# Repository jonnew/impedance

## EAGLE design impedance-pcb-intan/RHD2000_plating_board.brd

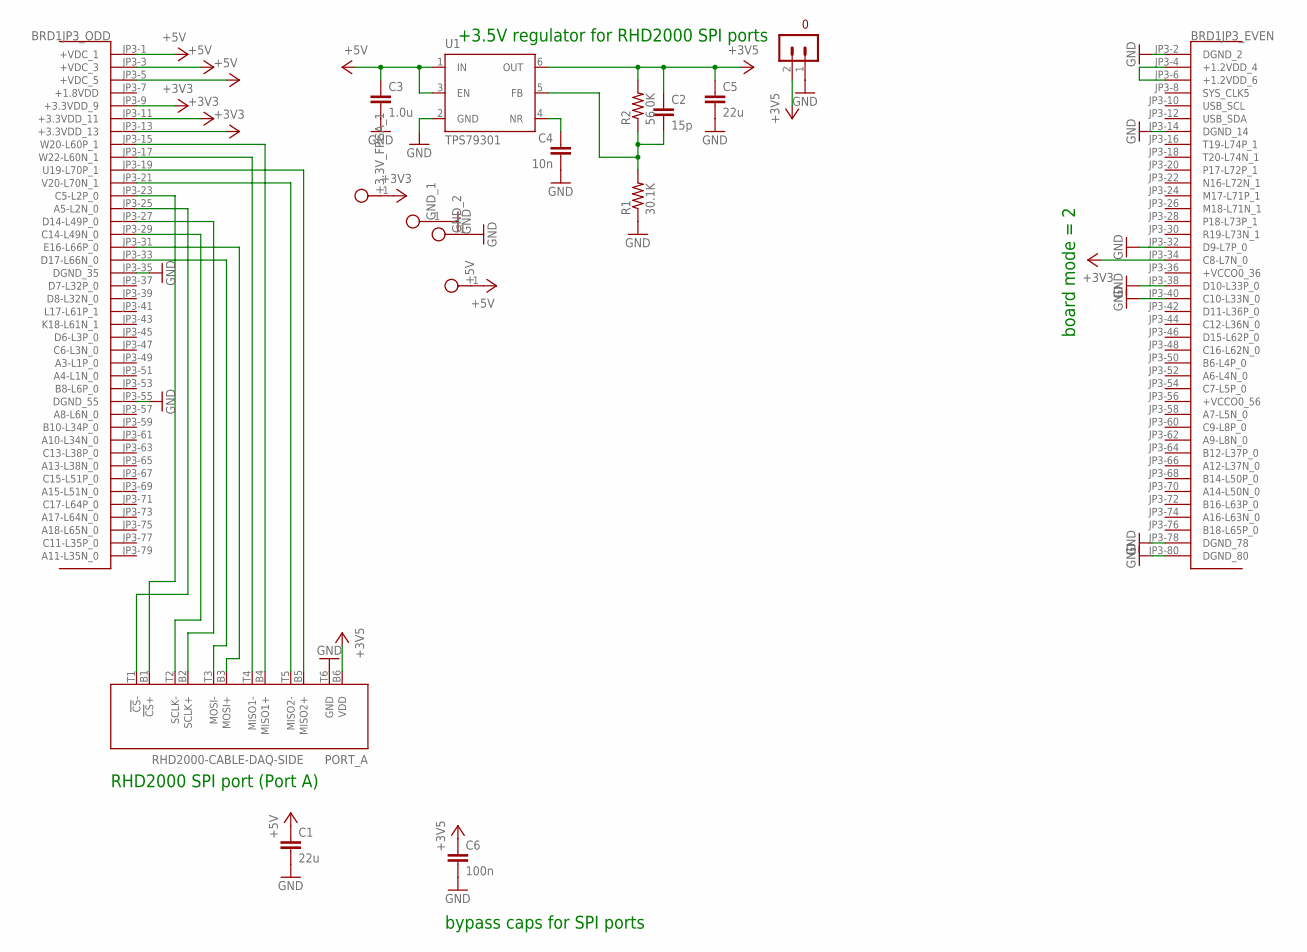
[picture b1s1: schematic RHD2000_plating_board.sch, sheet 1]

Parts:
+3.3V_FPGA_1, +5V: TESTPOINT
BRD1: OPALKELLY_XEM6010
C1, C5: 22u; 1206
C2: 15p; 0603
C3: 1.0u; 0805
C4: 10n; 0603
C6: 100n; 0603
GND_1, GND_2: TESTPOINT
PORT_A: RHD2000-CABLE-DAQ-SIDE; OMNETICS_PZN-12-AA
R1: 30.1K; 0603
R2: 56.0K; 0603
S2: TERMINAL_BLOCK_2-3.5MM-3.5V; TERMINAL_BLOCK_3.5MM_2_3.5V
U1: TPS79301; SOT-23-6

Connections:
+1.8VDD: BRD1.JP3-7 (+1.8VDD)
+3V3: +3.3V_FPGA_1.1, BRD1.JP3-9 (+3.3VDD_9), BRD1.JP3-11 (+3.3VDD_11), BRD1.JP3-13 (+3.3VDD_13), BRD1.JP3-34 (C8-L7N_0); also elsewhere on the board
+3V5: C2.1, C5.1, C6.1, PORT_A.B6 (VDD), R2.2, S2.2 (1), U1.6 (OUT)
+5V: +5V.1, BRD1.JP3-1 (+VDC_1), BRD1.JP3-3 (+VDC_3), BRD1.JP3-5 (+VDC_5), C1.1, C3.1, U1.1 (IN), U1.3 (EN); also elsewhere on the board
+VCCO0_36: BRD1.JP3-36 (+VCCO0_36)
+VCCO0_56: BRD1.JP3-56 (+VCCO0_56)
+VCCO1_35: BRD1.JP2-35 (+VCCO1_35)
+VCCO1_55: BRD1.JP2-55 (+VCCO1_55)
GND: BRD1.JP3-2 (DGND_2), BRD1.JP3-14 (DGND_14), BRD1.JP3-32 (D9-L7P_0), BRD1.JP3-35 (DGND_35), BRD1.JP3-38 (D10-L33P_0), BRD1.JP3-40 (C10-L33N_0), BRD1.JP3-55 (DGND_55), BRD1.JP3-78 (DGND_78), BRD1.JP3-80 (DGND_80), C1.2, C3.2, C4.2, C5.2, C6.2, GND_1.1, GND_2.1, PORT_A.T6 (GND), R1.1, S2.1 (0), U1.2 (GND); also elsewhere on the board
unnamed: BRD1.JP3-15 (W20-L60P_1), PORT_A.B4 (MISO1+)
unnamed: BRD1.JP3-17 (W22-L60N_1), PORT_A.T4 (MISO1-)
unnamed: BRD1.JP3-19 (U19-L70P_1), PORT_A.B5 (MISO2+)
unnamed: BRD1.JP3-21 (V20-L70N_1), PORT_A.T5 (MISO2-)
unnamed: BRD1.JP3-23 (C5-L2P_0), PORT_A.B1 (!CS!+)
unnamed: BRD1.JP3-25 (A5-L2N_0), PORT_A.T1 (!CS!-)
unnamed: BRD1.JP3-27 (D14-L49P_0), PORT_A.B2 (SCLK+)
unnamed: BRD1.JP3-29 (C14-L49N_0), PORT_A.T2 (SCLK-)
unnamed: BRD1.JP3-31 (E16-L66P_0), PORT_A.B3 (MOSI+)
unnamed: BRD1.JP3-33 (D17-L66N_0), PORT_A.T3 (MOSI-)
unnamed: C4.1, U1.4 (NR)
unnamed: C2.2, R1.2, R2.1, U1.5 (FB)
unnamed: BRD1.JP3-4 (+1.2VDD_4), BRD1.JP3-6 (+1.2VDD_6)

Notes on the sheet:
+3.5V regulator for RHD2000 SPI ports
RHD2000 SPI port (Port A)
board mode = 2
bypass caps for SPI ports

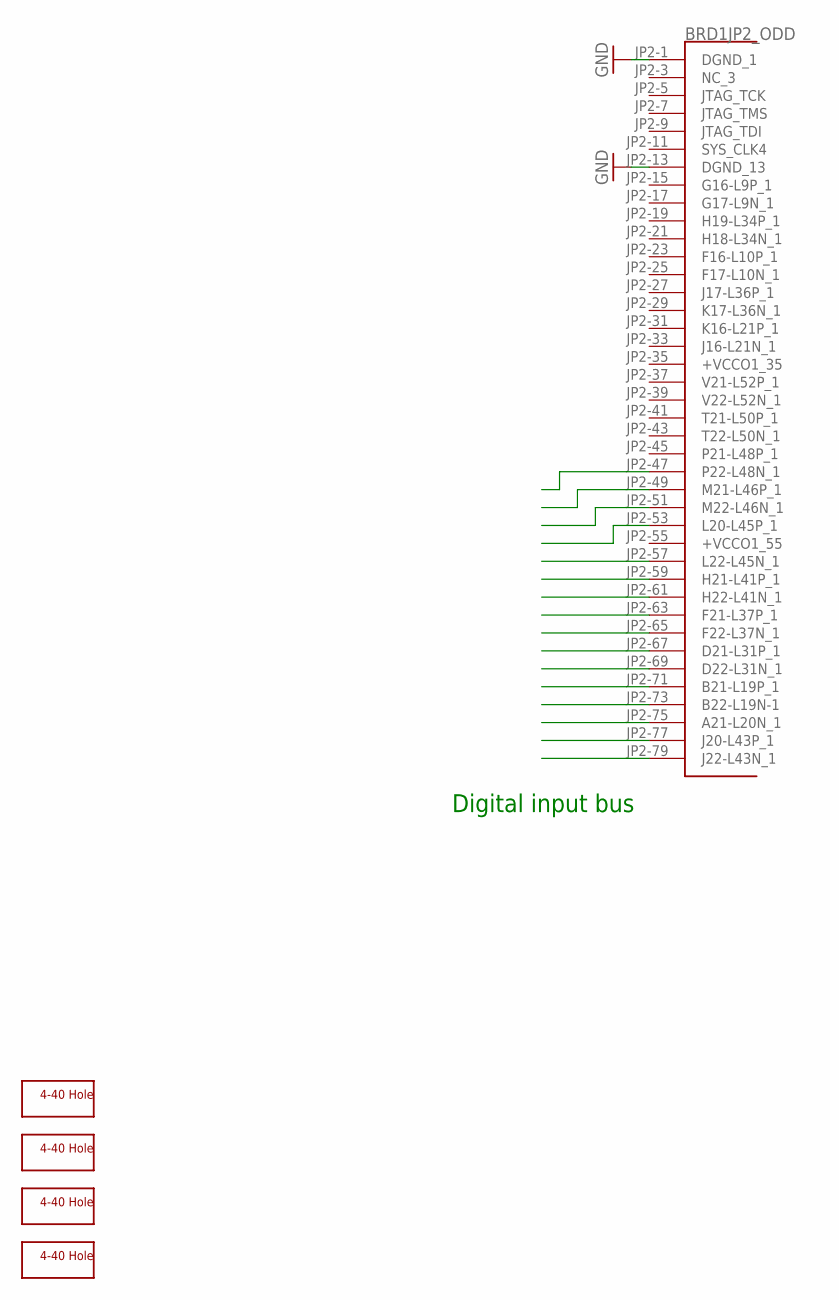
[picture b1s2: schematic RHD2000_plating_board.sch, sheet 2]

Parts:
BRD1: OPALKELLY_XEM6010
H1, H2, H3, H4: SCREW_HOLE_4-40

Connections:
+1.8VDD: BRD1.JP3-7 (+1.8VDD)
+VCCO0_36: BRD1.JP3-36 (+VCCO0_36)
+VCCO0_56: BRD1.JP3-56 (+VCCO0_56)
+VCCO1_35: BRD1.JP2-35 (+VCCO1_35)
+VCCO1_55: BRD1.JP2-55 (+VCCO1_55)
GND: BRD1.JP2-1 (DGND_1), BRD1.JP2-13 (DGND_13); also elsewhere on the board

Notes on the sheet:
Digital input bus

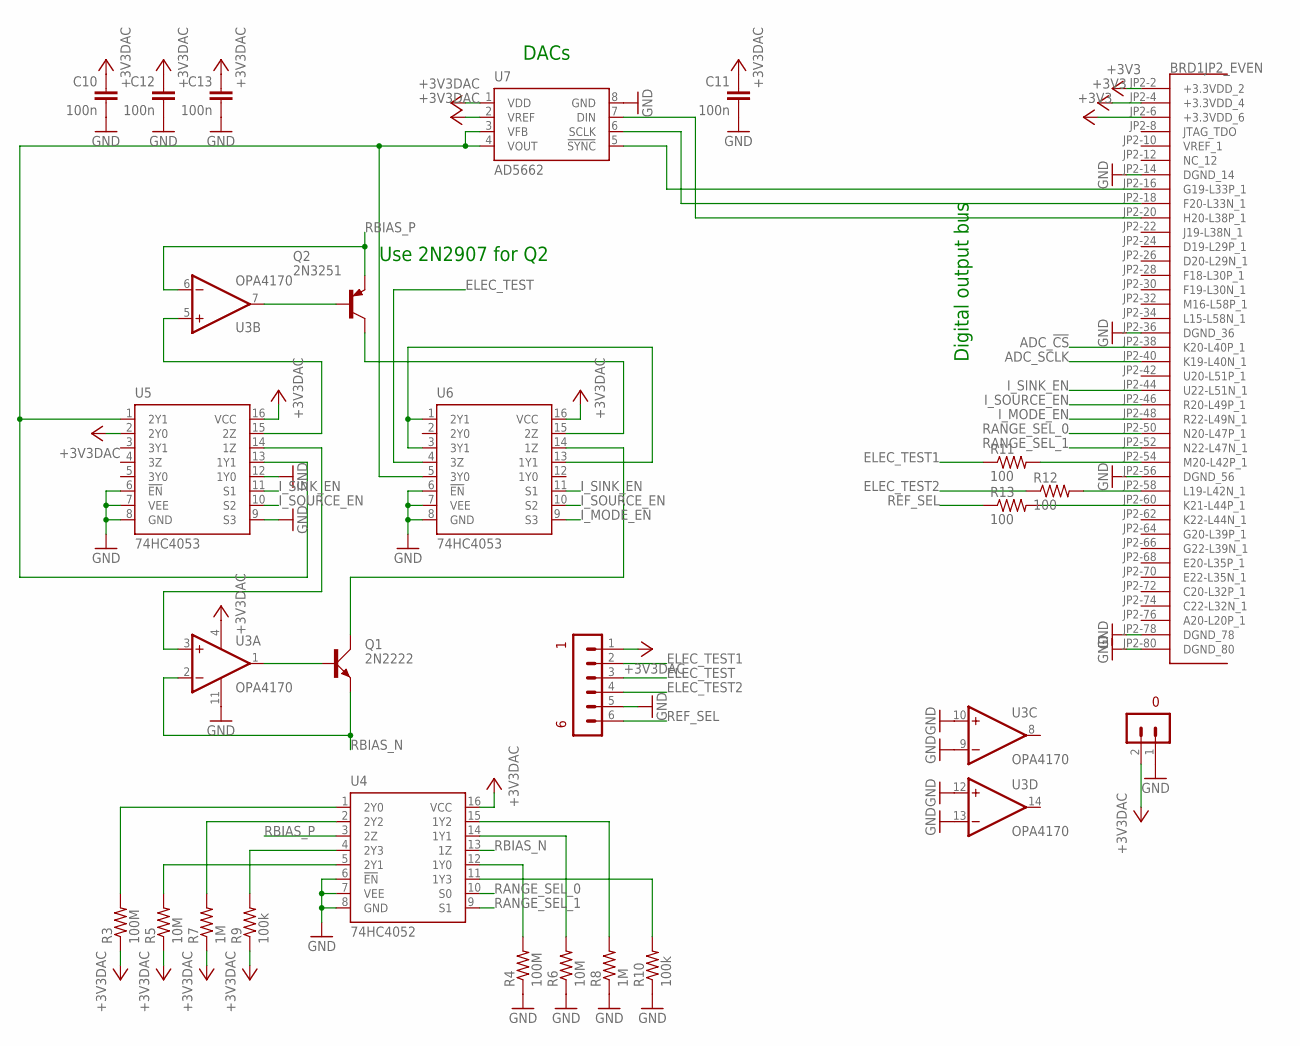
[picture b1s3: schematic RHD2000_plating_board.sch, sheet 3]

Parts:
BRD1: OPALKELLY_XEM6010
C10, C11, C12, C13: 100n; 0603
Q1: 2N2222; TO18A
Q2: 2N3251; TO18
R3, R4: 100M; 1206
R5, R6: 10M; 0603
R7, R8: 1M; 0603
R9, R10: 100k; 0603
R11, R12, R13: 100; 0603
S1: TERMINAL_BLOCK_2-3.5MM-3.3V; TERMINAL_BLOCK_3.5MM_2_3.3V
S3: WIRES-6
U3: OPA4170; SOIC-14
U4: 74HC4052; TSSOP-16
U5, U6: 74HC4053; TSSOP-16
U7: AD5662; SOT-23-RJ-8

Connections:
+1.8VDD: BRD1.JP3-7 (+1.8VDD)
+3V3: BRD1.JP2-2 (+3.3VDD_2), BRD1.JP2-4 (+3.3VDD_4), BRD1.JP2-6 (+3.3VDD_6); also elsewhere on the board
+3V3DAC: C10.1, C11.1, C12.1, C13.1, R3.1, R5.1, R7.1, R9.1, S1.2 (1), S3.1, U3.4 (V+), U4.16 (VCC), U5.2 (2Y0), U5.16 (VCC), U6.16 (VCC), U7.1 (VDD), U7.2 (VREF); also elsewhere on the board
+VCCO0_36: BRD1.JP3-36 (+VCCO0_36)
+VCCO0_56: BRD1.JP3-56 (+VCCO0_56)
+VCCO1_35: BRD1.JP2-35 (+VCCO1_35)
+VCCO1_55: BRD1.JP2-55 (+VCCO1_55)
ADC_!CS!: BRD1.JP2-38 (K20-L40P_1)
ADC_SCLK: BRD1.JP2-40 (K19-L40N_1)
ELEC_TEST: S3.3, U6.4 (3Z)
ELEC_TEST1: R11.1, S3.2
ELEC_TEST2: R12.1, S3.4
GND: BRD1.JP2-14 (DGND_14), BRD1.JP2-36 (DGND_36), BRD1.JP2-56 (DGND_56), BRD1.JP2-78 (DGND_78), BRD1.JP2-80 (DGND_80), C10.2, C11.2, C12.2, C13.2, R4.1, R6.1, R8.1, R10.1, S1.1 (0), S3.5, U3.9 (-IN), U3.10 (+IN), U3.11 (V-), U3.12 (+IN), U3.13 (-IN), U4.6 (!EN!), U4.7 (VEE), U4.8 (GND), U5.6 (!EN!), U5.7 (VEE), U5.8 (GND), U5.9 (S3), U5.12 (1Y0), U6.6 (!EN!), U6.7 (VEE), U6.8 (GND), U7.8 (GND); also elsewhere on the board
I_MODE_EN: BRD1.JP2-48 (R22-L49N_1), U6.9 (S3)
I_SINK_EN: BRD1.JP2-44 (U22-L51N_1), U5.11 (S1), U6.11 (S1)
I_SOURCE_EN: BRD1.JP2-46 (R20-L49P_1), U5.10 (S2), U6.10 (S2)
unnamed: Q1.B, U3.1 (OUT)
unnamed: U5.1 (2Y1), U5.13 (1Y1), U6.5 (3Y0), U7.3 (VFB), U7.4 (VOUT)
unnamed: U3.3 (+IN), U5.14 (1Z)
unnamed: Q1.C, U6.14 (1Z)
unnamed: U3.5 (+IN), U5.15 (2Z)
unnamed: Q2.2 (B), U3.7 (OUT)
unnamed: Q2.3 (C), U6.15 (2Z)
unnamed: BRD1.JP2-54 (M20-L42P_1), R11.2
unnamed: BRD1.JP2-58 (L19-L42N_1), R12.2
unnamed: R9.2, U4.4 (2Y3)
unnamed: R7.2, U4.2 (2Y2)
unnamed: R5.2, U4.5 (2Y1)
unnamed: R3.2, U4.1 (2Y0)
unnamed: R4.2, U4.12 (1Y0)
unnamed: R6.2, U4.14 (1Y1)
unnamed: R8.2, U4.15 (1Y2)
unnamed: R10.2, U4.11 (1Y3)
unnamed: U6.1 (2Y1), U6.3 (3Y1), U6.13 (1Y1)
unnamed: BRD1.JP2-60 (K21-L44P_1), R13.2
unnamed: BRD1.JP2-16 (G19-L33P_1), U7.5 (!SYNC!)
unnamed: BRD1.JP2-18 (F20-L33N_1), U7.6 (SCLK)
unnamed: BRD1.JP2-20 (H20-L38P_1), U7.7 (DIN)
RANGE_SEL_0: BRD1.JP2-50 (N20-L47P_1), U4.10 (S0)
RANGE_SEL_1: BRD1.JP2-52 (N22-L47N_1), U4.9 (S1)
RBIAS_N: Q1.E, U3.2 (-IN), U4.13 (1Z)
RBIAS_P: Q2.1 (E), U3.6 (-IN), U4.3 (2Z)
REF_SEL: R13.1, S3.6

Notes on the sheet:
DACs
Digital output bus
Use 2N2907 for Q2

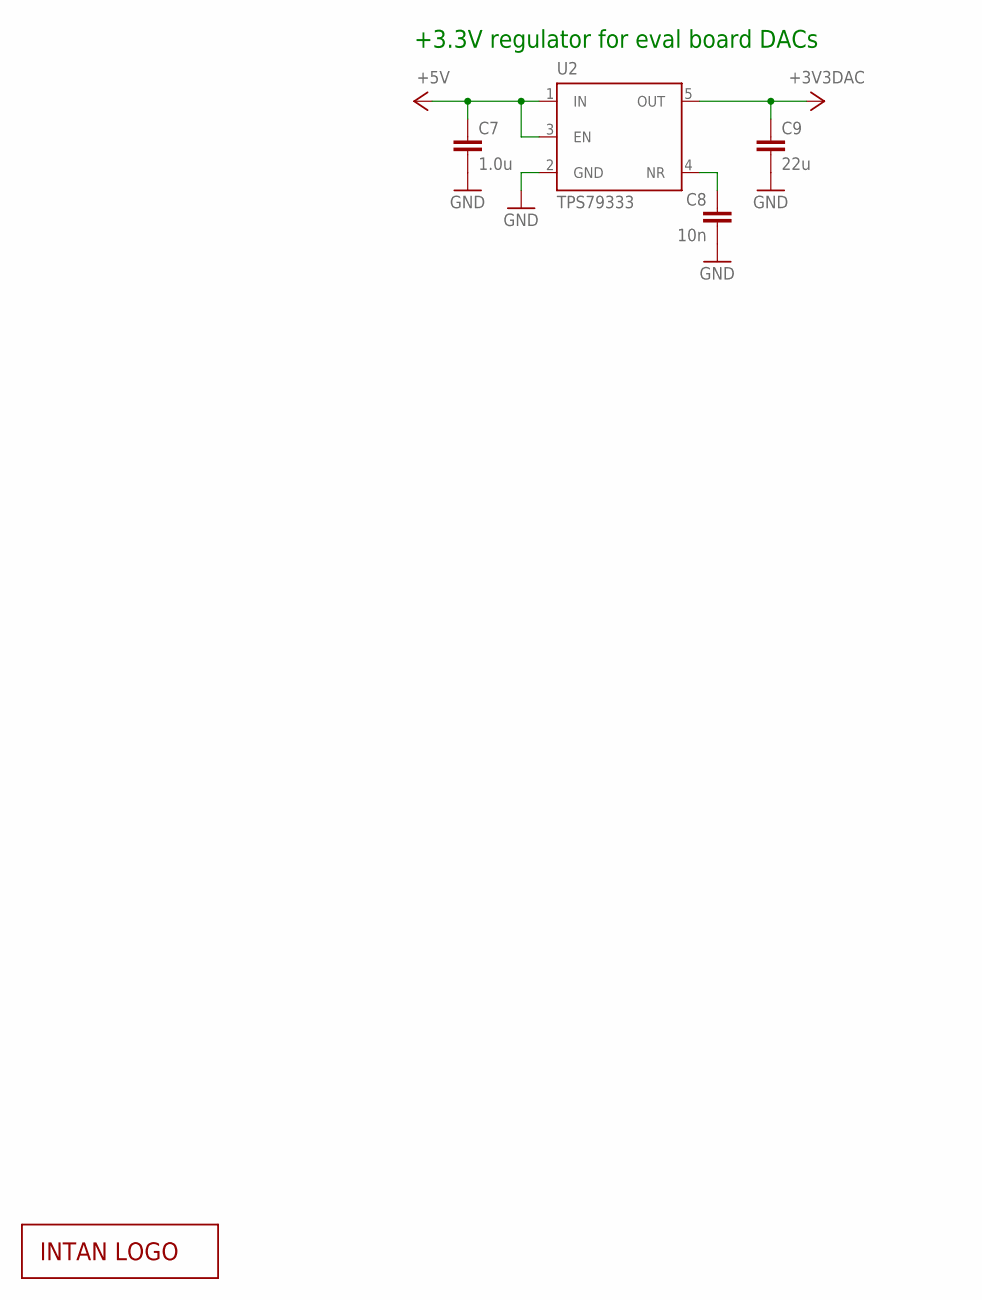
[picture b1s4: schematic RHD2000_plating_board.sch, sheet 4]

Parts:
C7: 1.0u; 0805
C8: 10n; 0603
C9: 22u; 1206
LOGO1: INTAN_LOGO
U2: TPS79333; SOT-23-5

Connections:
+3V3DAC: C9.1, U2.5 (OUT); also elsewhere on the board
+5V: C7.1, U2.1 (IN), U2.3 (EN); also elsewhere on the board
GND: C7.2, C8.2, C9.2, U2.2 (GND); also elsewhere on the board
unnamed: C8.1, U2.4 (NR)

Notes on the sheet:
+3.3V regulator for eval board DACs

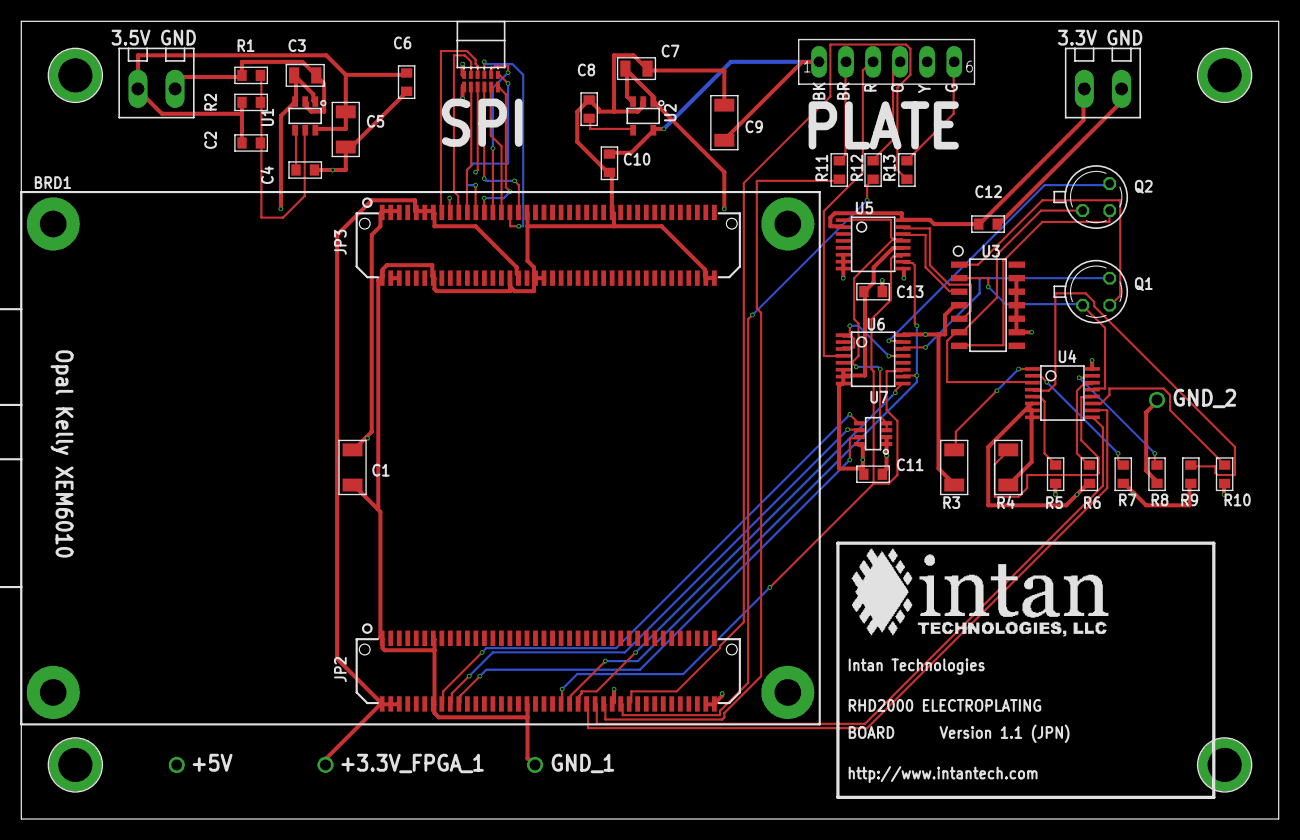
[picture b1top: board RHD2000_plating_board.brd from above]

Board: 4 copper layers, 118.1 x 74.9 mm, 49 parts (0 on the bottom side), 52 nets.

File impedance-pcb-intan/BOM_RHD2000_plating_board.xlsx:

Bill of Materials |  | RHD2000 Plating Board |  | Intan Technologies, LLC
Part | Value | Device | Package | Digi-Key part number | Notes | X (mm) | Y (mm) | Angle | Side | SMD/thru-hole
BRD1 | XEM6010-LX45 | USB/FPGA interface board | module | Opal Kelly XEM6010-LX45 | do not populate
C1 | 22 uF | ceramic capacitor | 1206 | 490-5527-1-ND |  | 31.12 | 33.020000000000003 | 270 | top | SMD
C2 | 15 pF | ceramic capacitor | 0603 | 399-1051-1-ND |  | 21.59 | 63.5 | 0 | top | SMD
C3 | 1.0 uF | ceramic capacitor | 0805 | 587-2910-1-ND |  | 26.67 | 69.849999999999994 | 0 | top | SMD
C4 | 10 nF | ceramic capacitor | 0603 | 478-1227-1-ND |  | 26.67 | 60.96 | 0 | top | SMD
C5 | 22 uF | ceramic capacitor | 1206 | 490-5527-1-ND |  | 30.48 | 64.77 | 270 | top | SMD
C6 | 100 nF | ceramic capacitor | 0603 | 490-1524-1-ND |  | 36.200000000000003 | 69.22 | 270 | top | SMD
C7 | 1.0 uF | ceramic capacitor | 0805 | 587-2910-1-ND |  | 57.79 | 70.48 | 0 | top | SMD
C8 | 10 nF | ceramic capacitor | 0603 | 478-1227-1-ND |  | 53.34 | 66.67 | 90 | top | SMD
C9 | 22 uF | ceramic capacitor | 1206 | 490-5527-1-ND |  | 66.040000000000006 | 65.41 | 90 | top | SMD
C10 | 100 nF | ceramic capacitor | 0603 | 490-1524-1-ND |  | 55.25 | 61.6 | 270 | top | SMD
C11 | 100 nF | ceramic capacitor | 0603 | 490-1524-1-ND |  | 80.010000000000005 | 32.380000000000003 | 180 | top | SMD
C12 | 100 nF | ceramic capacitor | 0603 | 490-1524-1-ND |  | 90.81 | 55.88 | 0 | top | SMD
C13 | 100 nF | ceramic capacitor | 0603 | 490-1524-1-ND |  | 80.010000000000005 | 49.53 | 180 | top | SMD
JP2 | Samtec BTE-040-01-F-D-A | 80-pin connector | SMD 0.8mm pitch | Newark 89M7080 |  | 49.53 | 13.97 | 0 | top | SMD
JP3 | Samtec BTE-040-01-F-D-A | 80-pin connector | SMD 0.8mm pitch | Newark 89M7080 |  | 49.53 | 53.85 | 0 | top | SMD
PORT A | PZN-12-AA | nano connector | polarized 12-pin | Omnetics A79623-001 |  | 43.18 | 69.33 | 0 | top | SMD
Q1 | BC107 | NPN bipolar transistor | TO-18-3 | BC107CS-ND |  | 100.97 | 49.53 | 0 | top | thru-hole | or 2N2222
Q2 | 2N3964 | PNP bipolar transistor | TO-18-3 | 2N3964-ND |  | 100.97 | 58.42 | 0 | top | thru-hole | or 2N2907
R1 | 30.1K (1%) | resistor | 0603 | P30.1KHCT-ND |  | 21.59 | 69.849999999999994 | 0 | top | SMD
R2 | 56.0K (1%) | resistor | 0603 | P56.0KHCT-ND |  | 21.59 | 67.31 | 180 | top | SMD
R3 | 100M (1%) | resistor | 1206 | CRHV100MACT-ND |  | 87.63 | 33.020000000000003 | 90 | top | SMD
R4 | 100M (1%) | resistor | 1206 | CRHV100MACT-ND |  | 92.71 | 33.020000000000003 | 90 | top | SMD
R5 | 10.0M (1%) | resistor | 0603 | 541-10.0MHCT-ND |  | 97.16 | 32.380000000000003 | 90 | top | SMD
R6 | 10.0M (1%) | resistor | 0603 | 541-10.0MHCT-ND |  | 100.33 | 32.380000000000003 | 90 | top | SMD
R7 | 1.00M (1%) | resistor | 0603 | P1.00MHCT-ND |  | 103.51 | 32.380000000000003 | 90 | top | SMD
R8 | 1.00M (1%) | resistor | 0603 | P1.00MHCT-ND |  | 106.68 | 32.380000000000003 | 90 | top | SMD
R9 | 100K (1%) | resistor | 0603 | 541-100KHCT-ND |  | 109.86 | 32.380000000000003 | 90 | top | SMD
R10 | 100K (1%) | resistor | 0603 | 541-100KHCT-ND |  | 113.03 | 32.380000000000003 | 90 | top | SMD
R11 | 100 | resistor | 0603 | P100GCT-ND |  | 76.84 | 60.96 | 270 | top | SMD
R12 | 100 | resistor | 0603 | P100GCT-ND |  | 80.010000000000005 | 60.96 | 270 | top | SMD
R13 | 100 | resistor | 0603 | P100GCT-ND |  | 83.19 | 60.96 | 270 | top | SMD
S1 | 2-pin | terminal block | 3.5mm thru-hole | ED1514-ND |  | 101.6 | 68.58 | 180 | top | thru-hole
S2 | 2-pin | terminal block | 3.5mm thru-hole | ED1514-ND |  | 12.7 | 68.58 | 180 | top | thru-hole
S3 | 6-pin wire leads | polarized nano connector | wire thru-hole | Omnetics A79605-001 | do not populate
U1 | TPS79301 | adjustable positive LDO regulator | SOT-23-6 | 296-12154-1-ND |  | 26.67 | 66.040000000000006 | 180 | top | SMD
U2 | TPS79333 | 3.3V LDO regulator | SOT-23-5 | 296-12961-1-ND |  | 58.42 | 66.040000000000006 | 180 | top | SMD
U3 | OPA4170 | quad rail-rail op-amp | SOIC-14 | 296-29664-1-ND |  | 90.81 | 48.26 | 270 | top | SMD
U4 | 74HC4052 | dual 4:1 MUX/DEMUX | TSSOP_16 | 568-8151-1-ND |  | 97.8 | 40 | 270 | top | SMD
U5 | 74HC4053 | triple 2:1 MUX/DEMUX | TSSOP_16 | 568-4478-1-ND |  | 80.02 | 53.97 | 270 | top | SMD
U6 | 74HC4053 | triple 2:1 MUX/DEMUX | TSSOP_16 | 568-4478-1-ND |  | 80.02 | 43.18 | 270 | top | SMD
U7 | AD5662 | 16-bit DAC | SOT-23-8 | AD5662BRJZ-2REEL7CT-ND |  | 80.010000000000005 | 36.200000000000003 | 90 | top | SMD

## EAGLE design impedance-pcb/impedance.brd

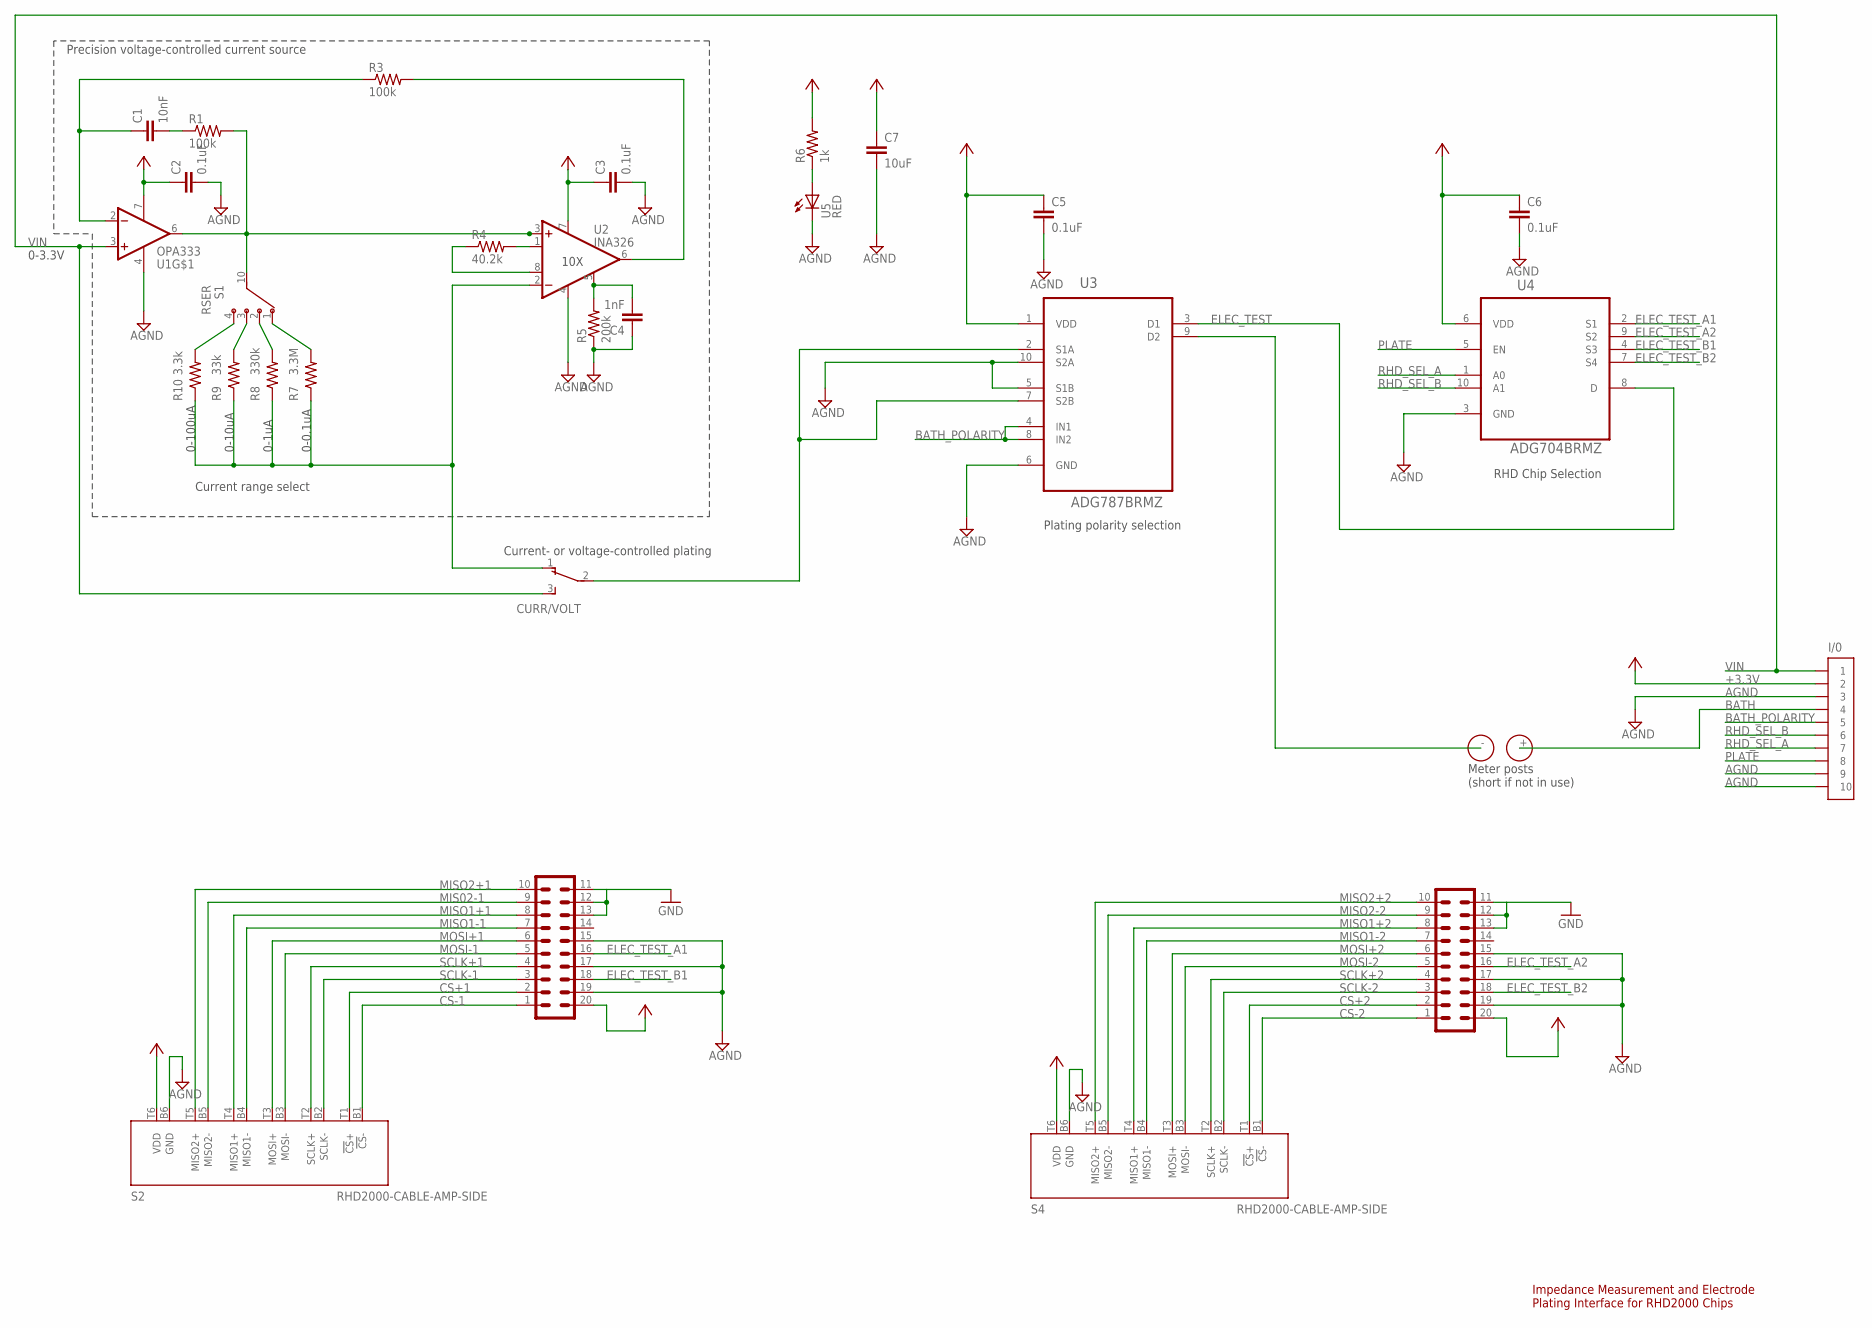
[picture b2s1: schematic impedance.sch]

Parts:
C1: 10nF; 0805
C2, C3, C5, C6: 0.1uF; 0805
C4: 1nF; 0805
C7: 10uF; 1206
CURR/VOLT: SPDT_PCM12; PCM12
HS1, HS2: JMD20-V
I/0: SCREW10_0.1-THRU; SCREW10
R1, R3: 100k; 0805
R4: 40.2k; 0805
R5: 200k; 0805
R6: 1k; 0805
R7: 3.3M; 0805
R8: 330k; 0805
R9: 33k; 0805
R10: 3.3k; 0805
S1: RSER; R-SWITCH
S2, S4: RHD2000-CABLE-AMP-SIDE; OMNETICS_PZN-12-AA
U1: OPA333; SOIC127P600X175-8N
U2: INA326; SOP65P490X110-8N
U3: ADG787BRMZ; SOP50P490X110-10N
U4: ADG704BRMZ; SOP50P490X110-10N
U5: RED; CHIP-LED0603
U$2: DUAL-POST_BANANA; BANANA-BINDING-POST

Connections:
+3.3V: C2.1, C3.1, C5.1, C6.1, C7.1, HS1.20, HS2.20, I/0.P$2 (2), R6.2, S2.T6 (VDD), S4.T6 (VDD), U1.7 (V+), U3.1 (VDD), U4.6 (VDD)
AGND: C2.2, C3.2, C4.1, C5.2, C6.2, C7.2, HS1.15, HS1.17, HS1.19, HS2.15, HS2.17, HS2.19, I/0.P$3 (3), I/0.P$9 (9), I/0.P$10 (10), R5.1, S2.B6 (GND), S4.B6 (GND), U1.4 (V-), U2.4 (V-), U3.5 (S1B), U3.6 (GND), U3.10 (S2A), U4.3 (GND), U5.C
BATH: I/0.P$4 (4), U$2.+ (1)
BATH_POLARITY: I/0.P$5 (5), U3.4 (IN1), U3.8 (IN2)
CS+1: HS1.2, S2.T1 (!CS!+)
CS+2: HS2.2, S4.T1 (!CS!+)
CS-1: HS1.1, S2.B1 (!CS!-)
CS-2: HS2.1, S4.B1 (!CS!-)
ELEC_TEST: U3.3 (D1), U4.8 (D)
ELEC_TEST_A1: HS1.16, U4.2 (S1)
ELEC_TEST_A2: HS2.16, U4.9 (S2)
ELEC_TEST_B1: HS1.18, U4.4 (S3)
ELEC_TEST_B2: HS2.18, U4.7 (S4)
GND: HS1.11, HS1.12, HS1.13, HS2.11, HS2.12, HS2.13
IOUT: CURR/VOLT.2, U3.2 (S1A), U3.7 (S2B)
MIS02-1: HS1.9, S2.B5 (MISO2-)
MISO1+1: HS1.8, S2.T4 (MISO1+)
MISO1+2: HS2.8, S4.T4 (MISO1+)
MISO1-1: HS1.7, S2.B4 (MISO1-)
MISO1-2: HS2.7, S4.B4 (MISO1-)
MISO2+1: HS1.10, S2.T5 (MISO2+)
MISO2+2: HS2.10, S4.T5 (MISO2+)
MISO2-2: HS2.9, S4.B5 (MISO2-)
MOSI+1: HS1.6, S2.T3 (MOSI+)
MOSI+2: HS2.6, S4.T3 (MOSI+)
MOSI-1: HS1.5, S2.B3 (MOSI-)
MOSI-2: HS2.5, S4.B3 (MOSI-)
unnamed: R1.2, S1.10 (COM), U1.6 (OUT), U2.3 (+IN)
unnamed: R4.2, U2.1 (R1_A)
unnamed: R4.1, U2.8 (R1_B)
unnamed: C1.2, R1.1
unnamed: C1.1, R3.1, U1.2 (-IN)
unnamed: R3.2, U2.6 (OUT)
unnamed: C4.2, R5.2, U2.5 (R2)
unnamed: R6.1, U5.A
unnamed: CURR/VOLT.1, R7.1, R8.1, R9.1, R10.1, U2.2 (-IN)
unnamed: R10.2, S1.4
unnamed: R9.2, S1.3
unnamed: R8.2, S1.2
unnamed: R7.2, S1.1
unnamed: U3.9 (D2), U$2.- (2)
PLATE: I/0.P$6 (6), U4.5 (EN)
RHD_SEL_A: I/0.P$7 (7), U4.1 (A0)
RHD_SEL_B: I/0.P$8 (8), U4.10 (A1)
SCLK+1: HS1.4, S2.T2 (SCLK+)
SCLK+2: HS2.4, S4.T2 (SCLK+)
SCLK-1: HS1.3, S2.B2 (SCLK-)
SCLK-2: HS2.3, S4.B2 (SCLK-)
VIN: CURR/VOLT.3, I/0.P$1 (1), U1.3 (+IN)

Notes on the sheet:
0-0.1uA
0-1uA
0-10uA
0-100uA
Current range select
0-3.3V
10X
Meter posts (short if not in use)
Current- or voltage-controlled plating
Impedance Measurement and Electrode Plating Interface for RHD2000 Chips
Plating polarity selection
RHD Chip Selection
Precision voltage-controlled current source

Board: 2 copper layers, 29 parts (0 on the bottom side), 49 nets, no tracks yet.

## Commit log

2014-11-05 Initial commit.
2014-11-06 Progress. It compiles now.
2014-11-07 Added skeleton for the plating side of the application.
2014-11-08 Started the pcb.
2014-11-08 Created plating/impedance testing circuit. Need to get parts to prototype it.
2014-12-23 Updated the impedance test interface schematic based on testing.
2014-12-28 Minor.
2014-12-31 Started implementing the plating control portion of the code. The application is a mess right now.
2015-01-01 I got the application working to some degree, then destroyed it while refactoring.
2015-01-01 We are back to pretty much functional with the code refactored. There is a very subtle and frustrating difference in accuracy between my code and the full RHD2000Interface code even though they seem 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
2015-01-02 Application is now functional. Time to test it with real tetrodes and a real plating setup.
2015-01-02 Started converting the impedance testing code to a library, but I have not worked the kinks out yet.
2015-01-03 Made several changes that make the application run on Linux. May want to tell Reid about some of these...
2015-01-04 Worked out some issues with the opal-kelly front panel libraries.
2015-01-04 Got rid of redundant lib.
2015-01-04 More ignore rules.
2015-01-07 Some changes to the command line program.
2015-01-08 Added an interactive mode to the application, data saving capabilities, and other mods. The app is broken right now.
2015-01-09 Numerous bug fixes and improvements to UI. Log files can now be saved.
2015-01-10 Numerous linux bug fixes, improvements to UI. Time to test again.
2015-01-11 Automatic plating class/routine added. Session loggin class added. Lots of refactoring.
2015-03-03 Added Intan's new board to the repo to see if I can just use that.
2015-07-29 Update to PCB design due to the screw header not fitting.
    - Made through holes slightly larger to accomindate 6-pin screw header.
    - Have to decide if I will puchase commerical software from Intan or
    revive my own application, which is very terrible at this point.
2016-06-11 Fixed reversed resistor labels in 3.5V regulator circuit.
2016-06-18 Added the Intan Matlab electroplating GUI code.
